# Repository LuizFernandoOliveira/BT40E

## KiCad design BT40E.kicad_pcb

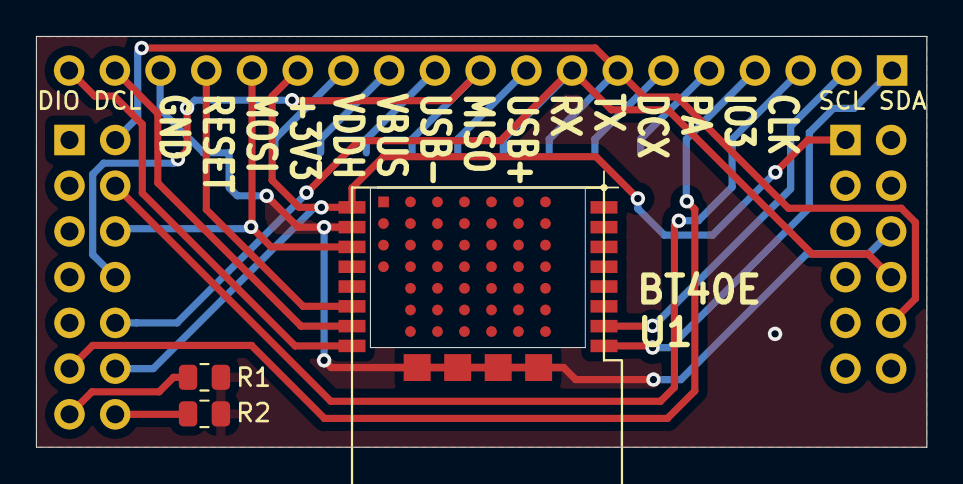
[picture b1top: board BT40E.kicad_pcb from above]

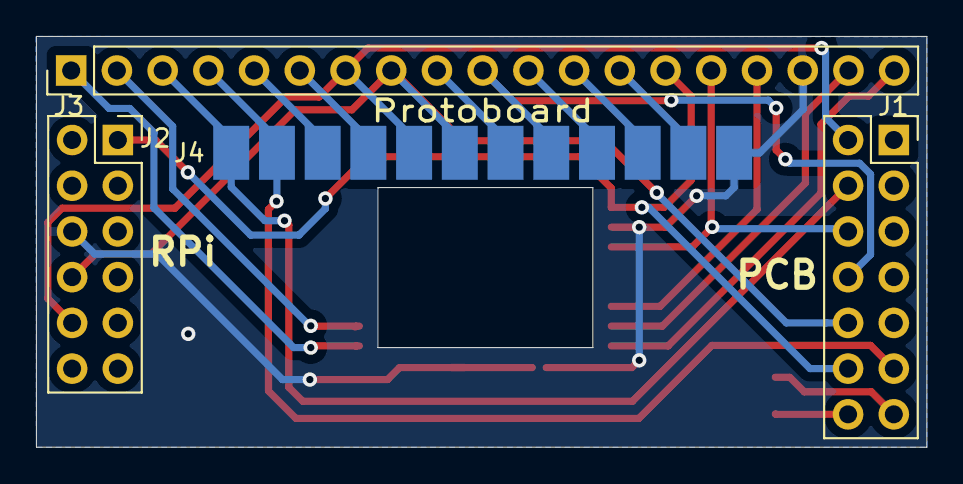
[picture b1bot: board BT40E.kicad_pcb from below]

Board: 2 copper layers, 49.5 x 22.8 mm, 7 parts (4 on the bottom side), 21 nets.

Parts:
J1: Conn_02x07_Odd_Even-Connector_Generic; PinSocket_2x07_P2.54mm_Vertical
J2: Conn_02x06_Odd_Even; PinSocket_2x06_P2.54mm_Vertical
J3: Conn_01x19; PinHeader_1x19_P2.54mm_Vertical
J4: Conn_01x12; PinHeader_1x12_P2.54mm_Vertical
R1, R2: 0R; R_0805_2012Metric
U1: BT40E; BT40F

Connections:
+3V3: J1.12, J2.1, J3.14, U1.P$9
GND: J2.6, J3.17, J4.12, R1.2, R2.2, U1.P$10, U1.P$A0, U1.P$B0, U1.P$C0, U1.P$D0, U1.P$H0, U1.P$H1, U1.P$H2, U1.P$H3
unnamed: J1.13, R1.1
unnamed: J1.14, R2.1
PA: J3.5, J4.3, U1.P$C3
RESET: J3.16, U1.P$14
RX: J1.10, J2.8, J3.8, J4.6, U1.P$D5
SCL: J3.2, U1.P$2
SDA: J3.1, U1.P$1
SPI_CLK: J1.4, J3.3, J4.1, U1.P$A3
SPI_DCX: J3.6, J4.4, U1.P$B5
SPI_IO3: J1.11, J3.4, J4.2, U1.P$A4
SPI_MISO: J1.8, J3.10, J4.8, U1.P$E6
SPI_MOSI: J1.6, J3.15, U1.P$11
SWDCLK: J3.18, U1.P$15
SWDIO: J3.19, U1.P$16
TX: J1.2, J2.10, J3.7, J4.5, U1.P$C5
USB_D+: J3.9, J4.7, U1.P$E4
USB_D-: J3.11, J4.9, U1.P$E5
VBUS: J3.12, J4.10, U1.P$F6
VDDH: J3.13, J4.11, U1.P$F4

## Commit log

2024-01-28 PCB finished
